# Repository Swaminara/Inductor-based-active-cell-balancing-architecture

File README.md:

# Inductor-based-active-cell-balancing-architecture
This repository contains the hardware design files of a modular inductor-based active cell balancing architecture proposed in CODES+ISSS '14 under the title "Verification of Balancing Architectures for Modular Batteries".

If you want to use the hardware files in this repository in your scientific publications, please reference it by the following bibtex citation

@inproceedings{lsn:2014,
  url = {  https://lukasiewycz.github.io/pdf/2014-CODES%2BISSS-Verification%20of%20Balancing%20Architectures%20for%20Modular%20Batteries.pdf  },
  doi = { 10.1145/2656075.2656104 },
  pages = { 30:1--30:10 },
  month = { 10 },
  year = { 2014 },
  location = { India },
  booktitle = { Proceedings of the 12th International Conference on Hardware/Software Codesign and System Synthesis (CODES+ISSS 2014) },
  author = { Martin Lukasiewycz and Sebastian Steinhorst and Swaminathan Narayanaswamy },
  title = { Verification of Balancing Architectures for Modular Batteries },
}

This repository is protected under the MIT license as attached.

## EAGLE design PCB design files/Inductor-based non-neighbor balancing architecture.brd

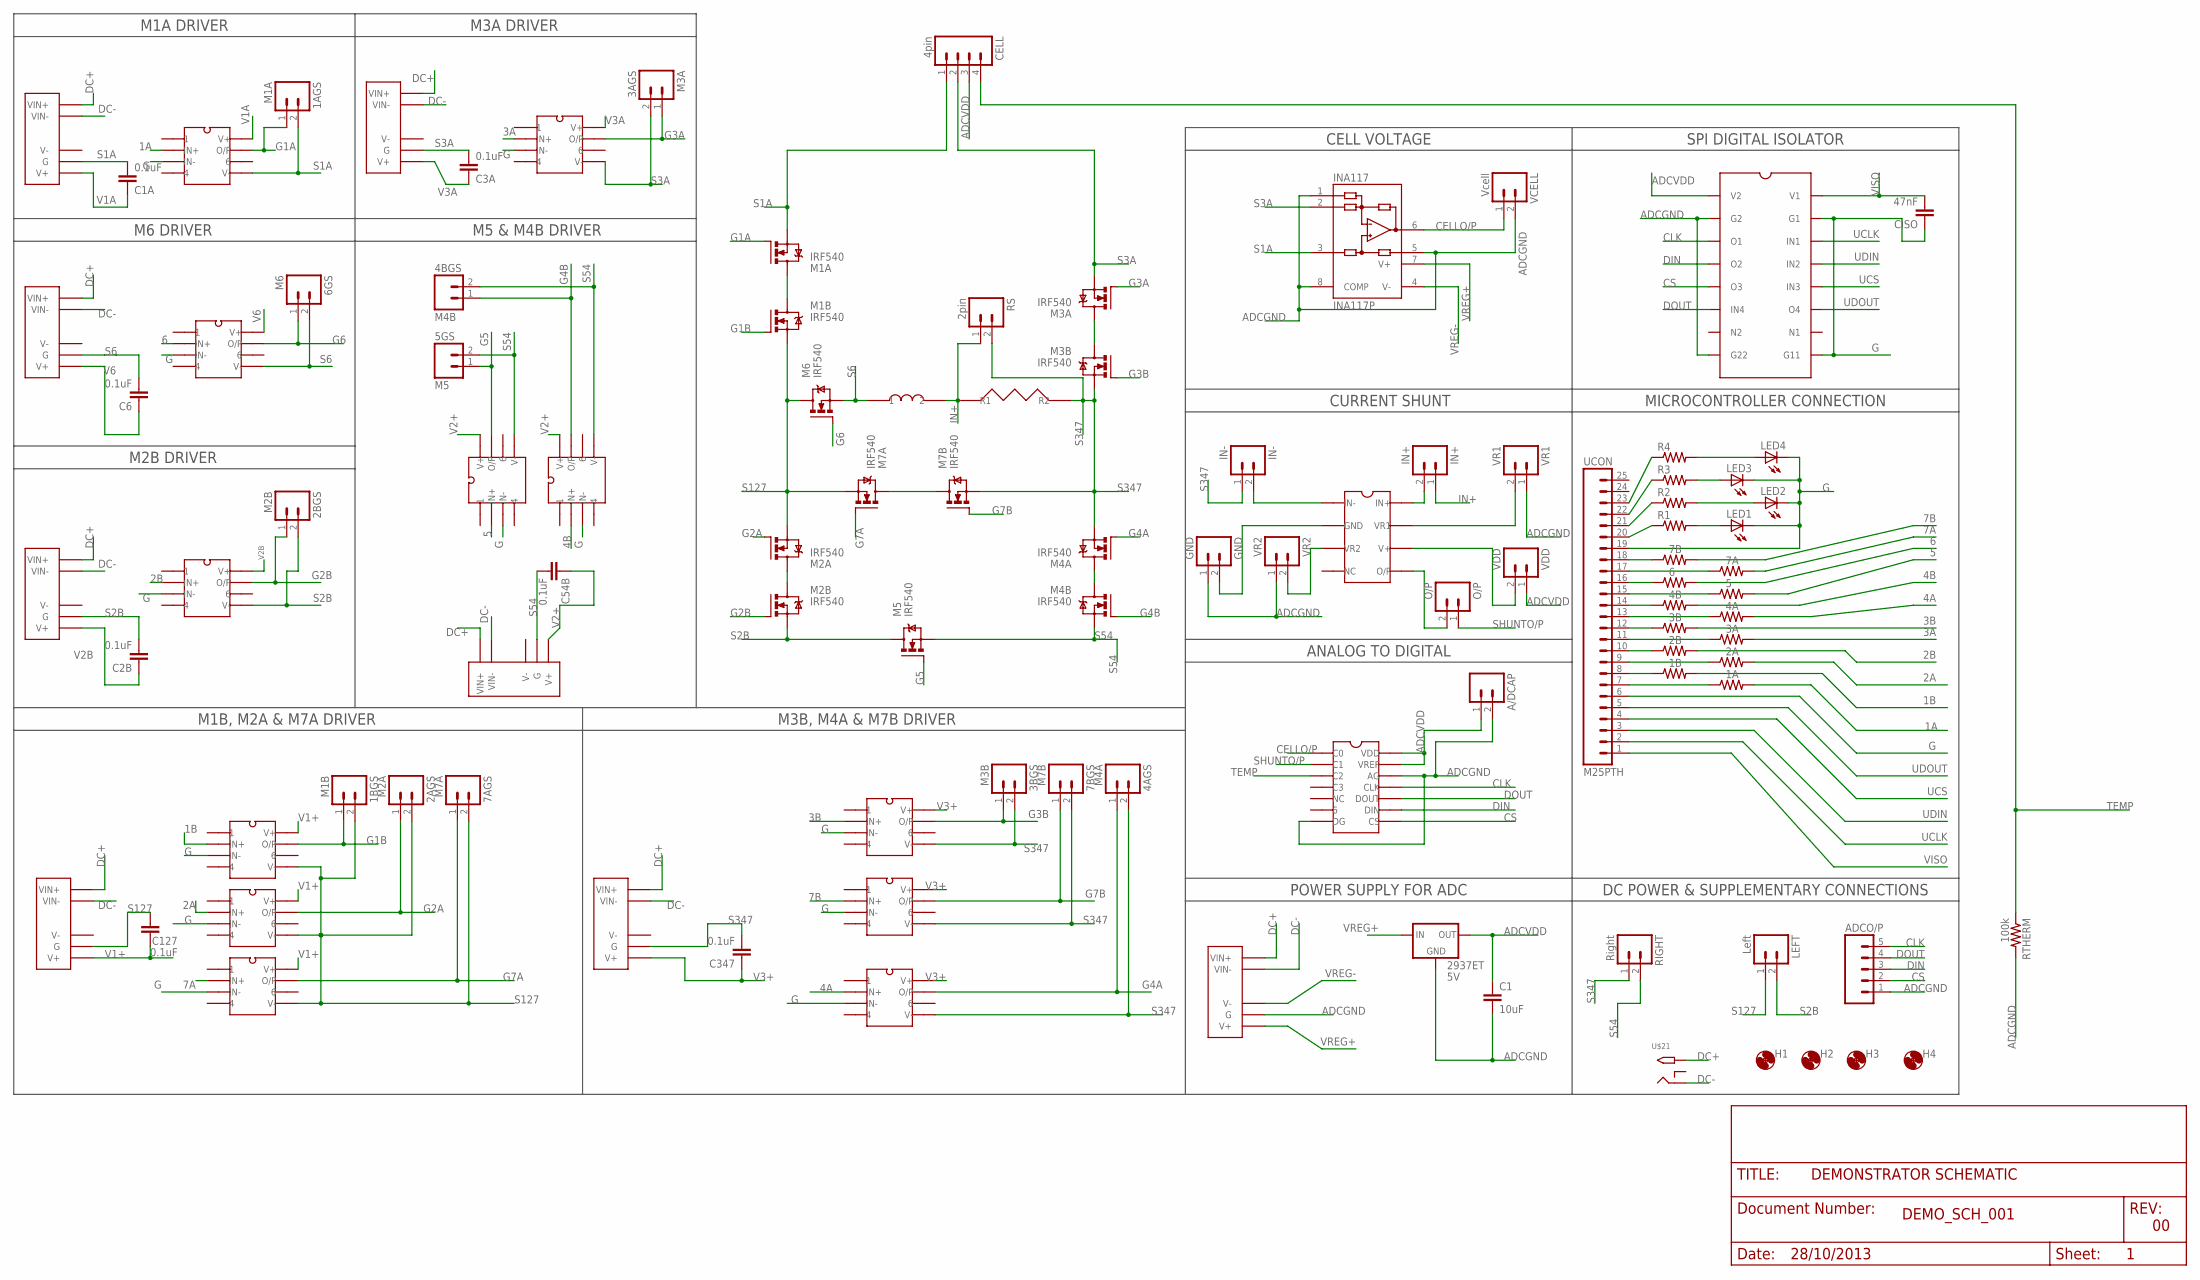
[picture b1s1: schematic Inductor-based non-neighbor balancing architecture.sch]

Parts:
1A, 1B, 2A, 2B, 3A, 3B, 4A, 4B, 5, 6, 7A, 7B: 220; AXIAL-0.5
1AGS: M1A; 1X02
1BGS: M1B; 1X02
2AGS: M2A; 1X02
2BGS: M2B; 1X02
3AGS: M3A; 1X02
3BGS: M3B; 1X02
4AGS: M4A; 1X02
4BGS: M4B; 1X02
5GS: M5; 1X02
6GS: M6; 1X02
7AGS: M7A; 1X02
7BGS: M7B; 1X02
2937ET: 5V; 78XXS
A/DCAP: M02PTH; 1X02
AD8210: CSM
ADC: ADC; DIL14
ADCO/P: M05PTH; 1X05
C1: 10uF; CAP-PTH-5MM
C1A, C2B, C3A, C6, C54B, C127, C347: 0.1uF; CAP-PTH-5MM
CELL: 4pin; 1X04
CISO: 47nF; CAP-PTH-5MM
DC/DC1A: 1A; DC-DC
DC/DC2B: 2B; DC-DC
DC/DC3A: 3A; DC-DC
DC/DC6: 6; DC-DC
DC/DC45: 4B5; DC-DC
DC/DC127: 1B2A7A; DC-DC
DC/DC347: 3B4A7B; DC-DC
DC/DC-ADC: ADC; DC-DC
GND: GND; 1X02
H1, H2, H3, H4: MOUNT-HOLE3.0; 3,0
HCPL902J: HCPL902
IN+: IN+; 1X02
IN-: IN-; 1X02
INA117: INA117P; DIL08
LED1, LED2, LED3, LED4: LEDCHIPLED_0805; CHIPLED_0805
LEFT: Left; 1X02
M1A, M1B, M2A, M2B, M3A, M3B, M4A, M4B, M5, M6, M7A, M7B: IRF540; TO220BV
M1AD: M1A; OPTO3180
M1BD: M1B; OPTO3180
M2AD: M2A; OPTO3180
M2BD: M2B; OPTO3180
M3AD: M3A; OPTO3180
M3BD: M3B; OPTO3180
M4AD: M4A; OPTO3180
M4BD: M4B; OPTO3180
M5D: M5; OPTO3180
M6D: M6; OPTO3180
M7AD: M7A; OPTO3180
M7BD: M7B; OPTO3180
O/P: O/P; 1X02
R1, R2, R3, R4: R-US_R0805; R0805
RIGHT: Right; 1X02
RS: 2pin; 1X02
RTHERM: 100k; AXIAL-0.5
U$1: INDFINAL; IND1MHFINAL
U$3: RSHUNT
U$21: 2.1MMJACKTHM; PJ-102A
UCON: M25PTH; 1X25
VCELL: Vcell; 1X02
VDD: VDD; 1X02
VR1: VR1; 1X02
VR2: VR2; 1X02

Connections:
1A: 1A.P$2 (2), M1AD.IN+
1B: 1B.P$2 (2), M1BD.IN+
2A: 2A.P$2 (2), M2AD.IN+
2B: 2B.P$2 (2), M2BD.IN+
3A: 3A.P$2 (2), M3AD.IN+
3B: 3B.P$2 (2), M3BD.IN+
4A: 4A.P$2 (2), M4AD.IN+
4B: 4B.P$2 (2), M4BD.IN+
5: 5.P$2 (2), M5D.IN+
6: 6.P$2 (2), M6D.IN+
7A: 7A.P$2 (2), M7AD.IN+
7B: 7B.P$2 (2), M7BD.IN+
ADCGND: 2937ET.GND, A/DCAP.2, ADC.AGND (AG), ADC.DGND (DG), ADCO/P.1, C1.2, DC/DC-ADC.G, GND.1, HCPL902J.G2, HCPL902J.G22, INA117.1 (REFB), INA117.5 (REFA), INA117.8 (COMP), RTHERM.P$2 (2), VCELL.2, VR1.1, VR2.1
ADCVDD: 2937ET.OUT, A/DCAP.1, ADC.VDD, ADC.VREF, C1.1, CELL.3, HCPL902J.V2, VDD.1
CELLO/P: ADC.CH0 (C0), INA117.6 (OUT), VCELL.1
CLK: ADC.CLK, ADCO/P.5, HCPL902J.OUT1 (O1)
CS: ADC.CS, ADCO/P.2, HCPL902J.OUT3 (O3)
DC+: DC/DC1A.VIN+, DC/DC2B.VIN+, DC/DC3A.VIN+, DC/DC6.VIN+, DC/DC45.VIN+, DC/DC127.VIN+, DC/DC347.VIN+, DC/DC-ADC.VIN+, U$21.TIP
DC-: DC/DC1A.VIN-, DC/DC2B.VIN-, DC/DC3A.VIN-, DC/DC6.VIN-, DC/DC45.VIN-, DC/DC127.VIN-, DC/DC347.VIN-, DC/DC-ADC.VIN-, U$21.RING
DIN: ADC.DIN, ADCO/P.3, HCPL902J.OUT2 (O2)
DOUT: ADC.DOUT, ADCO/P.4, HCPL902J.IN4
G: CISO.1, HCPL902J.G1, HCPL902J.G11, LED1.C, LED2.C, LED3.C, LED4.C, M1AD.IN-, M1BD.IN-, M2AD.IN-, M2BD.IN-, M3AD.IN-, M3BD.IN-, M4AD.IN-, M4BD.IN-, M5D.IN-, M6D.IN-, M7AD.IN-, M7BD.IN-, UCON.6, UCON.19
G1A: 1AGS.1, M1A.G, M1AD.O/P
G1B: 1BGS.1, M1B.G, M1BD.O/P
G2A: 2AGS.1, M2A.G, M2AD.O/P
G2B: 2BGS.1, M2B.G, M2BD.O/P
G3A: 3AGS.1, M3A.G, M3AD.O/P
G3B: 3BGS.1, M3B.G, M3BD.O/P
G4A: 4AGS.1, M4A.G, M4AD.O/P
G4B: 4BGS.1, M4B.G, M4BD.O/P
G5: 5GS.1, M5.G, M5D.O/P
G6: 6GS.1, M6.G, M6D.O/P
G7A: 7AGS.1, M7A.G, M7AD.O/P
G7B: 7BGS.1, M7B.G, M7BD.O/P
IN+: IN+.1, RS.1, U$1.2, U$3.R1
unnamed: M1A.D, M1B.D
unnamed: M4A.D, M4B.D
unnamed: AD8210.VR2, VR2.2
unnamed: M7A.D, M7B.D
unnamed: M2A.D, M2B.D
unnamed: AD8210.IN-, IN-.2
unnamed: AD8210.GND, GND.2
unnamed: AD8210.V+, VDD.2
unnamed: M3A.D, M3B.D
unnamed: AD8210.O/P, O/P.2
unnamed: AD8210.VR1, VR1.2
unnamed: AD8210.IN+, IN+.2
unnamed: 1A.P$1 (1), UCON.7
unnamed: 1B.P$1 (1), UCON.8
unnamed: 2A.P$1 (1), UCON.9
unnamed: 2B.P$1 (1), UCON.10
unnamed: 3A.P$1 (1), UCON.11
unnamed: 3B.P$1 (1), UCON.12
unnamed: 4A.P$1 (1), UCON.13
unnamed: 4B.P$1 (1), UCON.14
unnamed: 5.P$1 (1), UCON.15
unnamed: 6.P$1 (1), UCON.16
unnamed: 7A.P$1 (1), UCON.17
unnamed: 7B.P$1 (1), UCON.18
unnamed: LED2.A, R2.2
unnamed: LED1.A, R1.2
unnamed: LED4.A, R4.2
unnamed: R2.1, UCON.21
unnamed: R3.1, UCON.22
unnamed: LED3.A, R3.2
unnamed: R4.1, UCON.23
R4: R1.1, UCON.20
S1A: 1AGS.2, C1A.2, CELL.1, DC/DC1A.G, INA117.3 (+IN), M1A.S, M1AD.V-
S2B: 2BGS.2, C2B.2, DC/DC2B.G, LEFT.2, M2B.S, M2BD.V-, M5.D
S3A: 3AGS.2, C3A.2, CELL.2, DC/DC3A.G, INA117.2 (-IN), M3A.S, M3AD.V-
S6: 6GS.2, C6.2, DC/DC6.G, M6.S, M6D.V-, U$1.1
S54: 4BGS.2, 5GS.2, C54B.2, DC/DC45.G, M4B.S, M4BD.V-, M5.S, M5D.V-, RIGHT.2
S127: 1BGS.2, 2AGS.2, 7AGS.2, C127.2, DC/DC127.G, LEFT.1, M1B.S, M1BD.V-, M2A.S, M2AD.V-, M6.D, M7A.S, M7AD.V-
S347: 3BGS.2, 4AGS.2, 7BGS.2, C347.2, DC/DC347.G, IN-.1, M3B.S, M3BD.V-, M4A.S, M4AD.V-, M7B.S, M7BD.V-, RIGHT.1, RS.2, U$3.R2
SHUNTO/P: ADC.CH1 (C1), O/P.1
TEMP: ADC.CH2 (C2), CELL.4, RTHERM.P$1 (1)
UCLK: HCPL902J.IN1, UCON.2
UCS: HCPL902J.IN3, UCON.4
UDIN: HCPL902J.IN2, UCON.3
UDOUT: HCPL902J.OUT4 (O4), UCON.5
V1+: C127.1, DC/DC127.V+, M1BD.V+, M2AD.V+, M7AD.V+
V1A: C1A.1, DC/DC1A.V+, M1AD.V+
V2+: C54B.1, DC/DC45.V+, M4BD.V+, M5D.V+
V2B: C2B.1, DC/DC2B.V+, M2BD.V+
V3+: C347.1, DC/DC347.V+, M3BD.V+, M4AD.V+, M7BD.V+
V3A: C3A.1, DC/DC3A.V+, M3AD.V+
V6: C6.1, DC/DC6.V+, M6D.V+
VISO: CISO.2, HCPL902J.V1, UCON.1
VREG+: 2937ET.IN, DC/DC-ADC.V+, INA117.7 (V+)
VREG-: DC/DC-ADC.V-, INA117.4 (V-)

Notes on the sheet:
M1A DRIVER
M3A DRIVER
M6 DRIVER
M5 & M4B DRIVER
M2B DRIVER
M1B, M2A & M7A DRIVER
M3B, M4A & M7B DRIVER
CELL VOLTAGE
CURRENT SHUNT
ANALOG TO DIGITAL
SPI DIGITAL ISOLATOR
MICROCONTROLLER CONNECTION
POWER SUPPLY FOR ADC
DC POWER & SUPPLEMENTARY CONNECTIONS

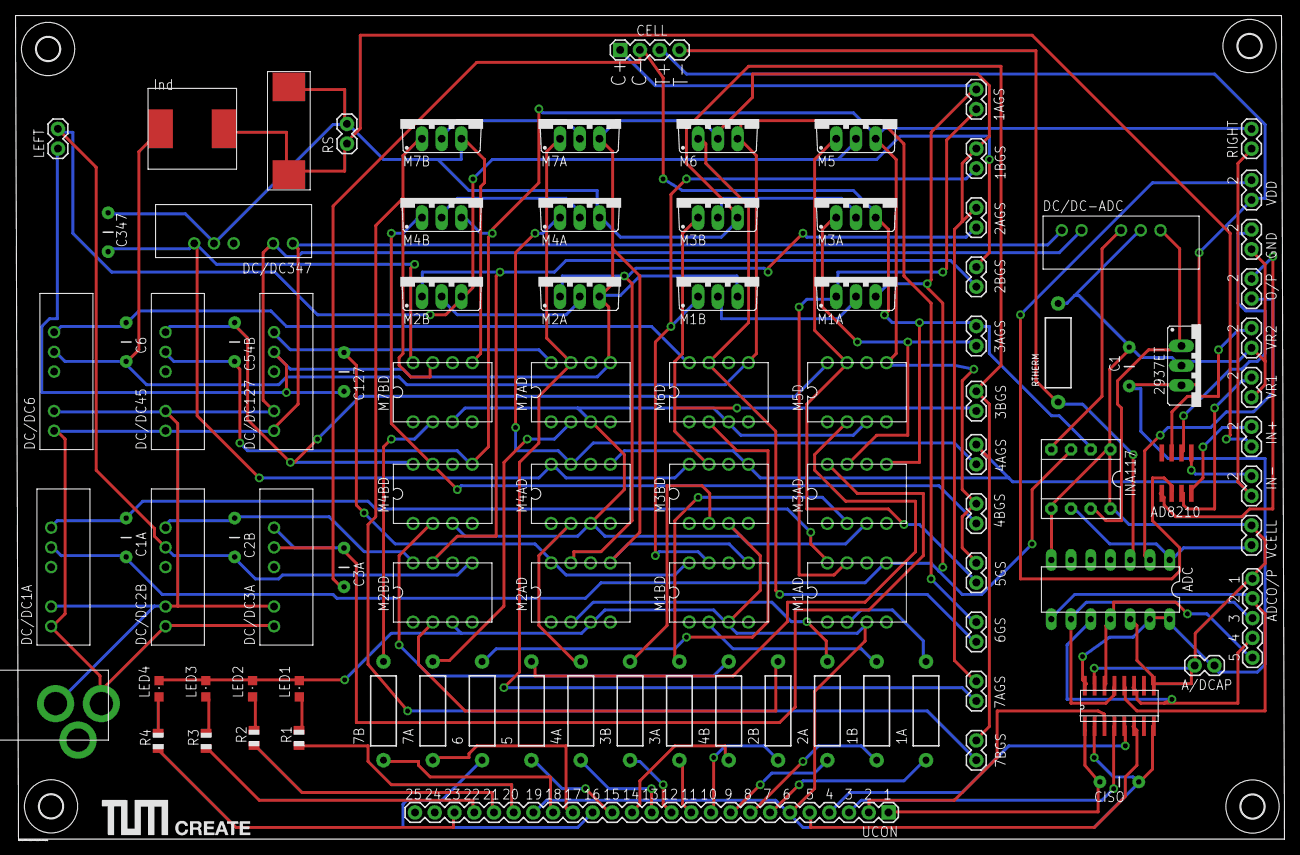
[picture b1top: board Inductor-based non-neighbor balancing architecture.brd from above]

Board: 2 copper layers, 163.4 x 106.0 mm, 101 parts (0 on the bottom side), 90 nets.

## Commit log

2016-02-23 created repository and added the hardware design files.

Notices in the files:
parts and their libraries:
SparkFun-Connectors: Licensing: CC v3.0 Share-Alike You are welcome to use this library for commercial purposes.
